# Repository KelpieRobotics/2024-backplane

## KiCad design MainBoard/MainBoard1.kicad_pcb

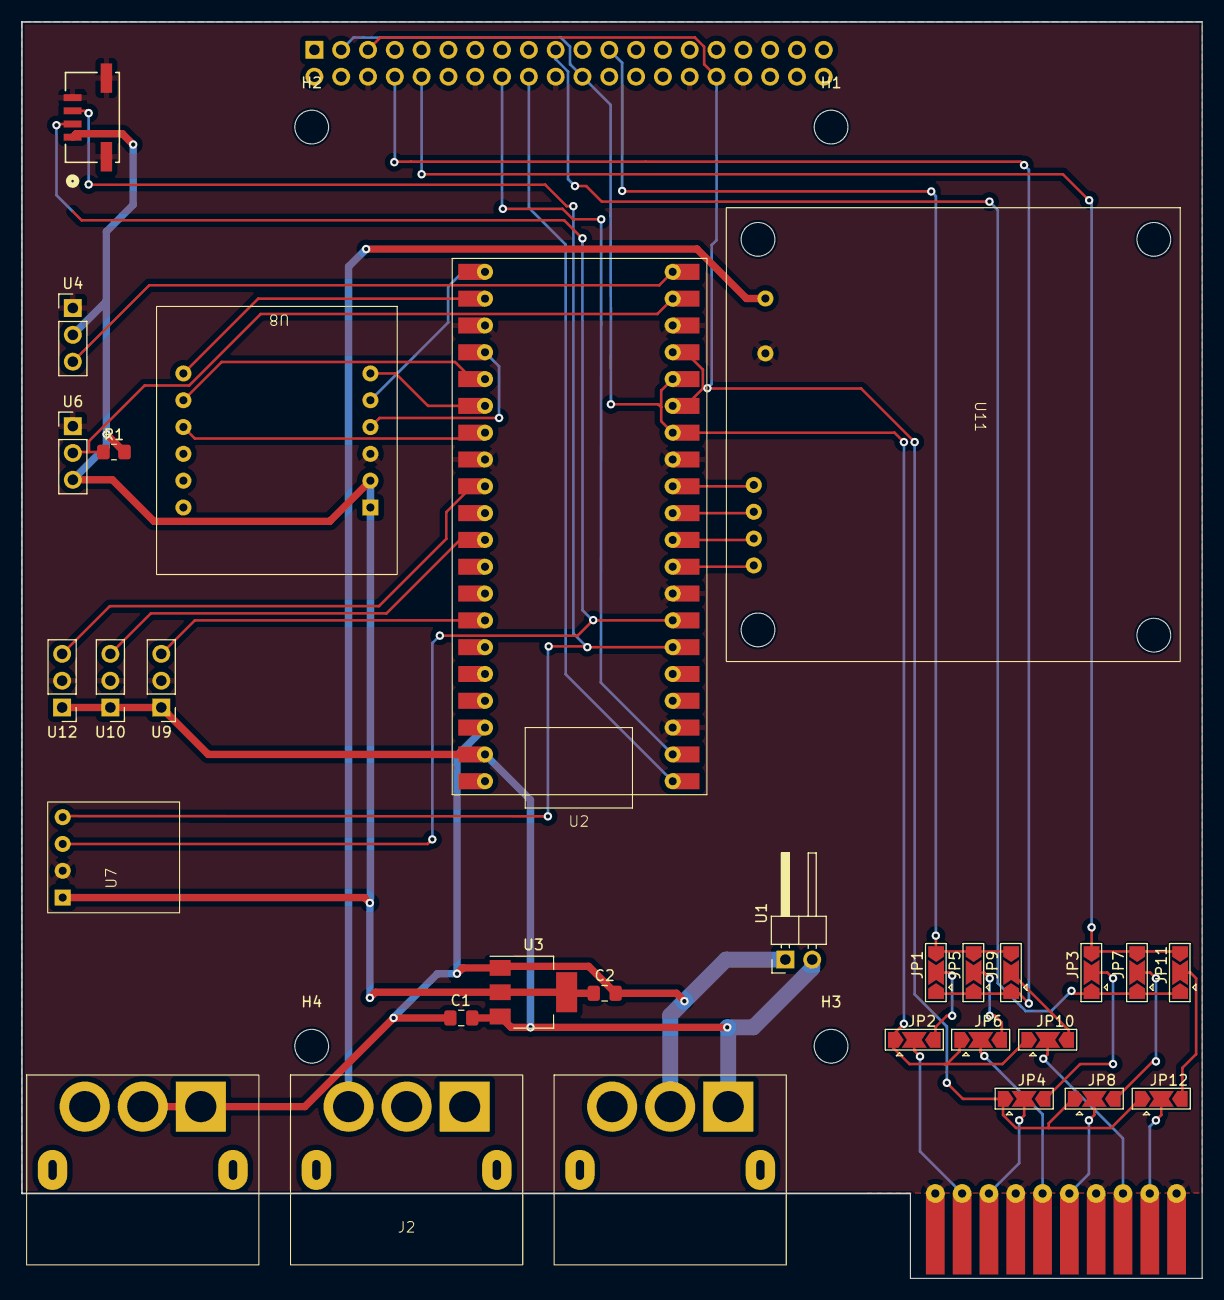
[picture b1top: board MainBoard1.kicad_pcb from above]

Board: 2 copper layers, 111.8 x 119.0 mm, 34 parts (1 on the bottom side), 42 nets.

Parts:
C1, C2: C; C_0805_2012Metric_Pad1.18x1.45mm_HandSolder
H1, H2, H3, H4: MountingHole; MountingHole_3.2mm_M3
J1: BAR02 Pressure Sensor; JST
J2: MR60PW-M_X3 (2)
J3: Conn_01x10_Pin; CardEdge_2x10 (2)
JP1, JP2, JP3, JP4, JP5, JP6, JP7, JP8, JP9, JP10, JP11, JP12: SolderJumper_3_Open; SolderJumper-3_P2.0mm_Open_TrianglePad1.0x1.5mm
R1: R; R_0805_2012Metric_Pad1.20x1.40mm_HandSolder
U1: PinHeader_1x02_P2.54mm_Horizontal
U2: Pi_Pico_1; ESP32-S3-Pico
U3: AMS1117-3.3; SOT-223-3_TabPin2
U4: Water Level Sensor; PinHeader_1x03_P2.54mm_Vertical
U5: Orange_Pi5+; PinHeader_2x20_P2.54mm_Vertical
U6: Temperature Sensor; PinHeader_1x03_P2.54mm_Vertical
U7: SHT30
U8: IMU
U9: Servo1; PinHeader_1x03_P2.54mm_Vertical
U10: Servo2; PinHeader_1x03_P2.54mm_Vertical
U11: L298N
U12: Servo3; PinHeader_1x03_P2.54mm_Vertical

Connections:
/5V: C1.2, J2.9 (C), U1.2 (5V), U2.39 (VSYS), U3.3 (VI), U9.1 (VIN), U10.1 (VIN), U12.1 (VIN)
/12V_1: J2.4 (A), U11.6 (12V)
/I2C1_SCL: JP4.1 (A), JP8.1 (A), JP12.1 (A), U2.15 (GP11), U2.17 (GP13), U5.5 (GPIO0_B7), U5.32 (GPIO1_A3)
/I2C1_SDA: JP2.1 (A), JP6.1 (A), JP10.1 (A), U2.14 (GP10), U2.16 (GP12), U5.3 (GPIO0_C0), U5.22 (GPIO1_A2)
/IMU_CS: U2.22 (GP17), U8.12 (CS)
/IMU_MISO: U2.21 (GP16), U8.5 (SDA)
/IMU_MOSI: U2.25 (GP19), U8.11 (DI)
/IMU_SCK: U2.24 (GP18), U8.4 (SCL)
/IN1: U2.12 (GP9), U11.1 (IN1)
/IN2: U2.11 (GP8), U11.2 (IN2)
/IN3: U2.10 (GP7), U11.3 (IN3)
/IN4: U2.9 (GP6), U11.4 (IN4)
/INT: U2.26 (GP20), U8.6 (INT)
/PICO_RX/TX_OPI: U2.2 (GP1), U5.16 (GPIO3_B5)
/PICO_TX/RX_OPI: U2.1 (GP0), U5.18 (GPIO3_B6)
/PWM_1: U2.34 (GP28), U9.3 (PWM)
/PWM_2: U2.31 (GP26), U10.3 (PWM)
/PWM_3: U2.29 (GP22), U12.3 (PWM)
/RST: U2.27 (GP21), U8.10 (RST)
/Sensor_Power: C2.1, J1.1 (VIN), R1.2, U3.2 (VO), U4.2 (VIN), U6.3 (Vdd), U7.1 (VIN), U8.1 (VIN), U8.2 (3Vo)
/Sensor_SCL: J1.2 (SCL), U2.7 (GP5), U7.3 (SCL)
/Sensor_SDA: J1.3 (SDA), U2.6 (GP4), U7.4 (SDA)
/Signal_0: R1.1, U2.19 (GP14), U6.2 (DQ)
/Signal_1: U2.20 (GP15), U4.3 (Signal)
/UART1_RX: JP3.1 (A), JP7.1 (A), JP11.1 (A), U5.19 (GPIO1_B2)
/UART1_TX: JP1.3 (B), JP5.3 (B), JP9.3 (B), U5.23 (GPIO1_B3)
/UART2_RX: JP3.3 (B), JP7.3 (B), JP11.3 (B), U5.10 (GPIO1_A0)
/UART2_TX: JP1.1 (A), JP5.1 (A), JP9.1 (A), U5.8 (GPIO1_A1)
/rx/scl_O1: J3.3, JP4.2 (C)
/rx/scl_O2: J3.6, JP8.2 (C)
/rx/scl_O3: J3.9, JP12.2 (C)
/tx/sda_O1: J3.2, JP2.2 (C)
/tx/sda_O2: J3.5, JP6.2 (C)
/tx/sda_O3: J3.8, JP10.2 (C)
GND1: J1.4 (GND), J1.5 (GND), J1.6 (GND), J3.1, J3.4, J3.7, J3.10, U2.3 (GND), U2.8 (GND), U2.13 (GND), U2.18 (GND), U2.23 (GND), U2.28 (GND), U4.1 (GND), U5.6 (GND), U5.9 (GND), U5.14 (GND), U5.20 (GND), U5.25 (GND), U5.30 (GND), U5.34 (GND), U6.1 (GND), U7.2 (GND), U8.3 (GND), U9.2 (GND2), U10.2 (GND2), U11.5 (GND), U12.2 (GND2)
GND2: C1.1, C2.2, J2.2 (B), J2.3 (C), J2.8 (B), U1.1 (GND), U2.38 (GND), U3.1 (GND)
unnamed: JP1.2 (C), JP2.3 (B)
unnamed: JP3.2 (C), JP4.3 (B)
unnamed: JP5.2 (C), JP6.3 (B)
unnamed: JP7.2 (C), JP8.3 (B)
unnamed: JP9.2 (C), JP10.3 (B)
unnamed: JP11.2 (C), JP12.3 (B)
